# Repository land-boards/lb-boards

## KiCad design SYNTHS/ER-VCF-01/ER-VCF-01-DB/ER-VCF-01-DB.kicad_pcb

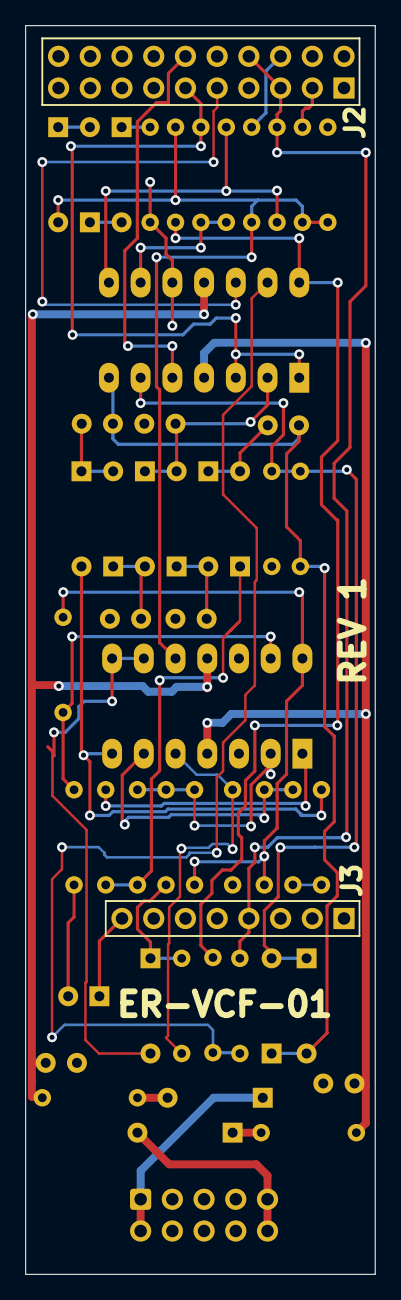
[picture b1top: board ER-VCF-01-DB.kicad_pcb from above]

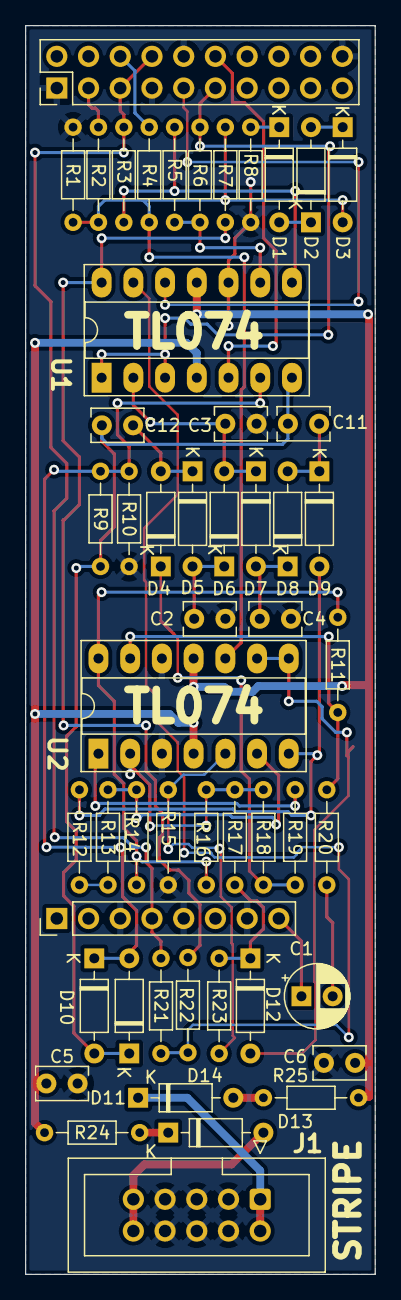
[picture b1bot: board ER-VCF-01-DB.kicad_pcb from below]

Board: 2 copper layers, 28.0 x 100.0 mm, 52 parts (52 on the bottom side), 41 nets.

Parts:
C1: 1uF; CP_Radial_D5.0mm_P2.50mm
C2, C3, C4, C11, C12: 1nF; C_Rect_L4.0mm_W2.5mm_P2.50mm
C5, C6: 0.1uF; C_Rect_L4.0mm_W2.5mm_P2.50mm
D1, D2, D3, D4, D5, D6, D7, D8, D9, D10, D11, D12, D13, D14: 1N4148; D_DO-35_SOD27_P7.62mm_Horizontal
J1: HEADER, 2X5; IDC-Header_2x05_P2.54mm_Vertical
J2: HEADER, 2X10; PinHeader_2x10_P2.54mm_Vertical
J3: HEADER, 1x8; PinHeader_1x08_P2.54mm_Vertical
R1, R9: 10K; R_Axial_DIN0204_L3.6mm_D1.6mm_P7.62mm_Horizontal
R2, R4, R7, R20, R21, R22: 100K; R_Axial_DIN0204_L3.6mm_D1.6mm_P7.62mm_Horizontal
R3, R6, R8, R11: 1K; R_Axial_DIN0204_L3.6mm_D1.6mm_P7.62mm_Horizontal
R5: 47K; R_Axial_DIN0204_L3.6mm_D1.6mm_P7.62mm_Horizontal
R10, R12, R19: 2.2K; R_Axial_DIN0204_L3.6mm_D1.6mm_P7.62mm_Horizontal
R13, R14, R15, R16, R17, R18, R23: 33K; R_Axial_DIN0204_L3.6mm_D1.6mm_P7.62mm_Horizontal
R24, R25: 10; R_Axial_DIN0204_L3.6mm_D1.6mm_P7.62mm_Horizontal
U1, U2: TL074; DIP-14_W7.62mm_Socket_LongPads

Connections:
+12V: C5.1, R24.2, U1.4 (V+), U2.4 (V+)
-12V: C6.2, R25.2, U1.11 (V-), U2.11 (V-)
/AUDIO: R11.2, R14.1, R16.1, U2.14
/CV: D12.1 (K), R17.1, R23.1
/J1-T: C1.1, J3.8
/J2-T: J2.5, J2.8, J3.4, R3.1, R21.1
/POT2-2: J2.9, U1.12 (+)
/POT4-2: J2.6, R4.1
/POT5-1: J2.11, R6.2, U1.1, U1.3 (+)
/POT5-2: J2.12, U1.5 (+)
/POT6-2: J2.3, R2.1
GND: C2.2, C3.2, C4.2, C5.2, C6.1, J1.3, J1.4, J1.5, J1.6, J1.7, J1.8, J2.1, J2.7, J2.10, J2.20, J3.3, J3.5, J3.7, R1.1, R8.1, R10.1, R15.1, U1.10 (+), U2.3 (+), U2.12 (+)
unnamed: C1.2, R20.1
unnamed: C2.1, D7.2 (A), D8.1 (K)
unnamed: C3.1, D6.2 (A), D7.1 (K), U1.2 (-)
unnamed: C4.1, D5.2 (A), D6.1 (K)
unnamed: C11.1, C12.1, D10.2 (A), D11.1 (K), R9.1, U1.7
unnamed: C11.2, D8.2 (A), D9.1 (K)
unnamed: C12.2, D4.2 (A), D5.1 (K)
unnamed: D1.1 (K), R8.2
unnamed: D1.2 (A), D2.1 (K)
unnamed: D2.2 (A), D3.1 (K)
unnamed: D3.2 (A), R1.2, R2.2, R4.2, R7.2, U2.10 (+)
unnamed: D4.1 (K), R18.2, R19.2
unnamed: D9.2 (A), R12.1, U2.7
unnamed: D10.1 (K), D11.2 (A), R9.2, R10.2, U1.6 (-)
unnamed: D12.2 (A), U2.8, U2.9 (-)
unnamed: D13.1 (K), R24.1
unnamed: D13.2 (A), J1.9, J1.10
unnamed: D14.1 (K), J1.1, J1.2
unnamed: D14.2 (A), R25.1
unnamed: R3.2, R5.2, U1.8
unnamed: R5.1, R6.1, U1.9 (-)
unnamed: R11.1, R20.2, U2.13 (-)
unnamed: R12.2, R13.2
unnamed: R13.1, R14.2, U2.6 (-)
unnamed: R15.2, R23.2, U2.5 (+)
unnamed: R16.2, R17.2, R18.1, U2.2 (-)
unnamed: R19.1, U2.1
unnamed: R21.2, R22.1, U1.13 (-)
unnamed: R7.1, R22.2, U1.14

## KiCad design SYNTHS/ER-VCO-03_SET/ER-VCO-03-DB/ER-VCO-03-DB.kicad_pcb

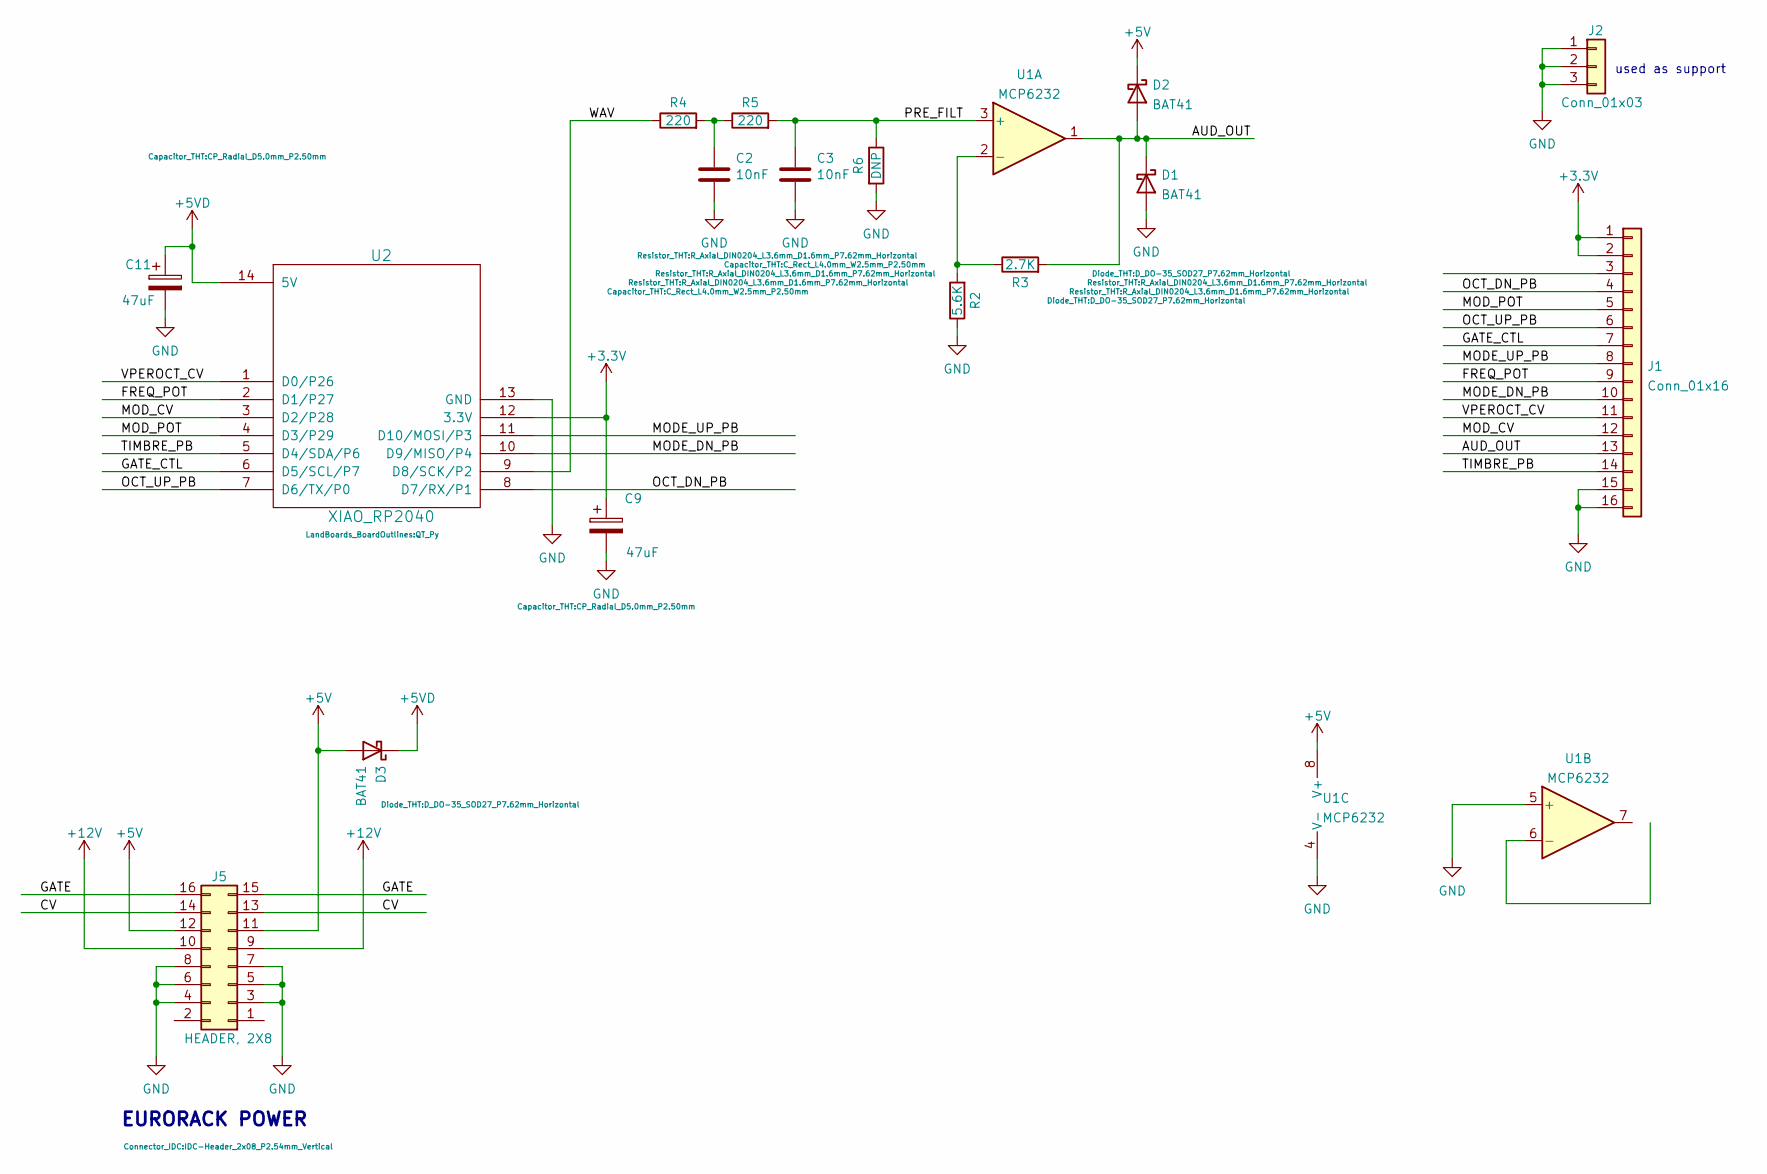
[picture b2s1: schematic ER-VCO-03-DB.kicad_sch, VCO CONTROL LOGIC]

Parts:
C2, C3: 10nF; C_Rect_L4.0mm_W2.5mm_P2.50mm
C9, C11: 47uF; CP_Radial_D5.0mm_P2.50mm
D1, D2, D3: BAT41; D_DO-35_SOD27_P7.62mm_Horizontal
J1: Conn_01x16; PinHeader_2x08_P2.54mm_Vertical
J2: Conn_01x03; PinHeader_1x03_P2.54mm_Vertical
J5: HEADER, 2X8; IDC-Header_2x08_P2.54mm_Vertical
R2: 5.6K; R_Axial_DIN0204_L3.6mm_D1.6mm_P7.62mm_Horizontal
R3: 2.7K; R_Axial_DIN0204_L3.6mm_D1.6mm_P7.62mm_Horizontal
R4, R5: 220; R_Axial_DIN0204_L3.6mm_D1.6mm_P7.62mm_Horizontal
R6: DNP; R_Axial_DIN0204_L3.6mm_D1.6mm_P7.62mm_Horizontal
U1: MCP6232; DIP-8_W7.62mm
U2: XIAO_RP2040; QT_Py

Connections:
+3V3: C9.1, J1.1, J1.2, U2.12 (3.3V)
+5V: D2.1 (K), D3.2 (A), J5.11, J5.12, U1.8 (V+)
+5VD: C11.1, D3.1 (K), U2.14 (5V)
+12V: J5.9, J5.10
/AUD_OUT: D1.1 (K), D2.2 (A), J1.13, R3.2, U1.1
/CV: J5.13, J5.14
/FREQ_POT: J1.9, U2.2 (D1/P27)
/GATE: J5.15, J5.16
/GATE_CTL: J1.7, U2.6 (D5/SCL/P7)
/MODE_DN_PB: J1.10, U2.10 (D9/MISO/P4)
/MODE_UP_PB: J1.8, U2.11 (D10/MOSI/P3)
/MOD_CV: J1.12, U2.3 (D2/P28)
/MOD_POT: J1.5, U2.4 (D3/P29)
/OCT_DN_PB: J1.4, U2.8 (D7/RX/P1)
/OCT_UP_PB: J1.6, U2.7 (D6/TX/P0)
/PRE_FILT: C3.1, R5.2, R6.1, U1.3 (+)
/TIMBRE_PB: J1.14, U2.5 (D4/SDA/P6)
/VPEROCT_CV: J1.11, U2.1 (D0/P26)
/WAV: R4.1, U2.9 (D8/SCK/P2)
GND: C2.2, C3.2, C9.2, C11.2, D1.2 (A), J1.15, J1.16, J2.1, J2.2, J2.3, J5.3, J5.4, J5.5, J5.6, J5.7, J5.8, R2.1, R6.2, U1.4 (V-), U1.5 (+), U2.13 (GND)
unnamed: C2.1, R4.2, R5.1
unnamed: R2.2, R3.1, U1.2 (-)

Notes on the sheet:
used as support
EURORACK POWER

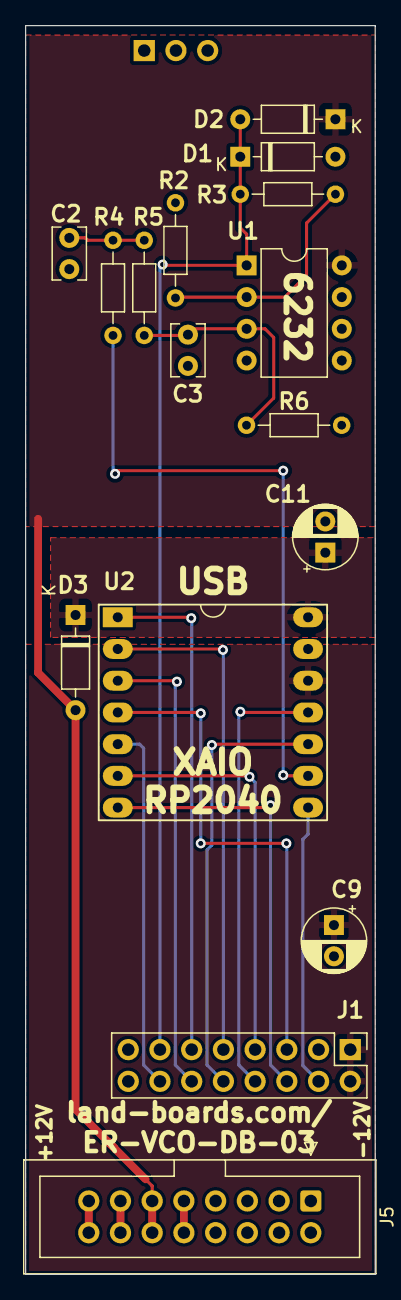
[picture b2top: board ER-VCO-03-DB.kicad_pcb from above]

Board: 2 copper layers, 28.0 x 100.0 mm, 17 parts (1 on the bottom side), 22 nets.

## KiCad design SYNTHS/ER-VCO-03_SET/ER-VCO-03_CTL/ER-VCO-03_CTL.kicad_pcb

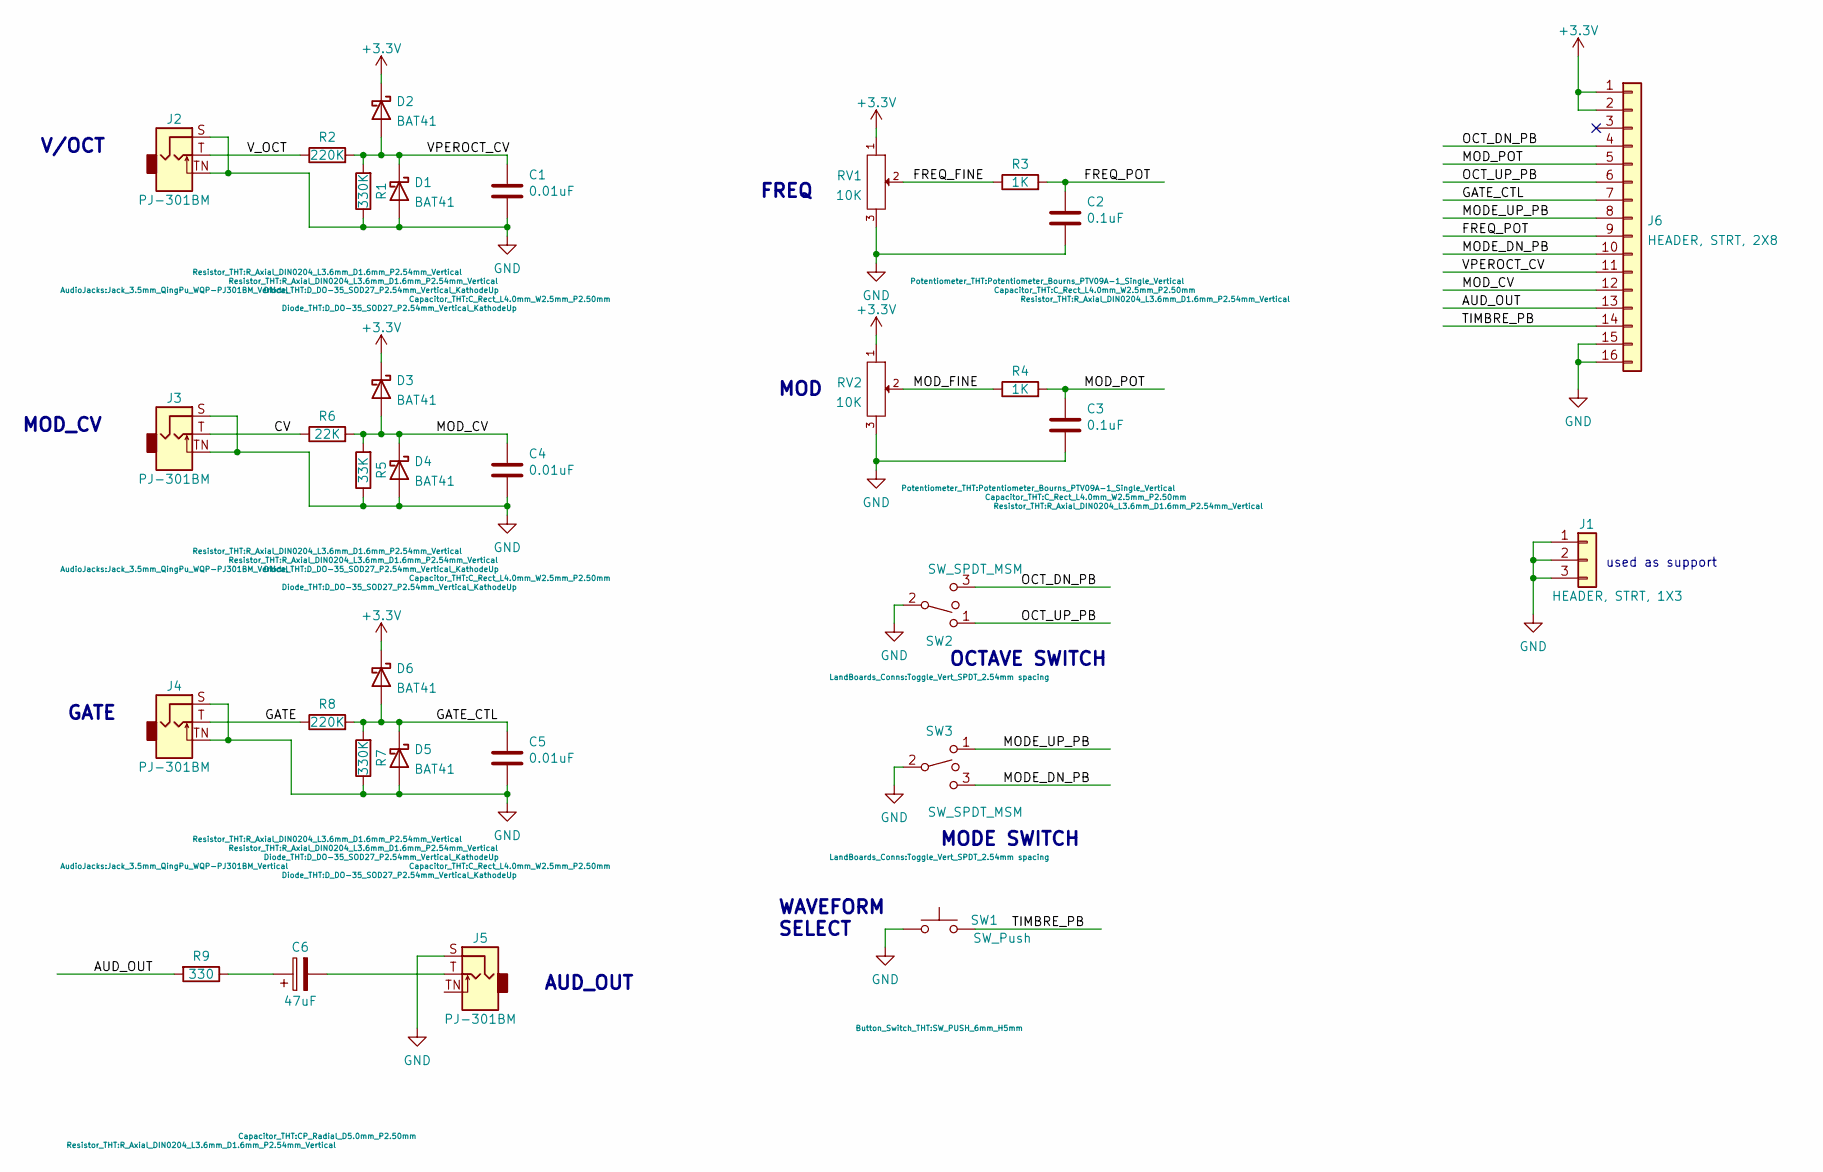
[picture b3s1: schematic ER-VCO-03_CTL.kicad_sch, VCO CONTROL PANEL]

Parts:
C1, C4, C5: 0.01uF; C_Rect_L4.0mm_W2.5mm_P2.50mm
C2, C3: 0.1uF; C_Rect_L4.0mm_W2.5mm_P2.50mm
C6: 47uF; CP_Radial_D5.0mm_P2.50mm
D1, D2, D3, D4, D5, D6: BAT41; D_DO-35_SOD27_P2.54mm_Vertical_KathodeUp
J1: HEADER, STRT, 1X3; PinHeader_1x03_P2.54mm_Vertical
J2, J3, J4, J5: PJ-301BM; Jack_3.5mm_QingPu_WQP-PJ301BM_Vertical
J6: HEADER, STRT, 2X8; PinHeader_2x08_P2.54mm_Vertical
R1, R7: 330K; R_Axial_DIN0204_L3.6mm_D1.6mm_P2.54mm_Vertical
R2, R8: 220K; R_Axial_DIN0204_L3.6mm_D1.6mm_P2.54mm_Vertical
R3, R4: 1K; R_Axial_DIN0204_L3.6mm_D1.6mm_P2.54mm_Vertical
R5: 33K; R_Axial_DIN0204_L3.6mm_D1.6mm_P2.54mm_Vertical
R6: 22K; R_Axial_DIN0204_L3.6mm_D1.6mm_P2.54mm_Vertical
R9: 330; R_Axial_DIN0204_L3.6mm_D1.6mm_P2.54mm_Vertical
RV1, RV2: 10K; Potentiometer_Bourns_PTV09A-1_Single_Vertical
SW1: SW_Push; SW_PUSH_6mm_H5mm
SW2, SW3: SW_SPDT_MSM; Toggle_Vert_SPDT_2.54mm spacing

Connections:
+3V3: D2.1 (K), D3.1 (K), D6.1 (K), J6.1, J6.2, RV1.1, RV2.1
/AUD_OUT: J6.13, R9.2
/CV: J3.T, R6.1
/FREQ_FINE: R3.1, RV1.2
/FREQ_POT: C2.1, J6.9, R3.2
/GATE: J4.T, R8.1
/GATE_CTL: C5.1, D5.1 (K), D6.2 (A), J6.7, R7.2, R8.2
/MODE_DN_PB: J6.10, SW3.3
/MODE_UP_PB: J6.8, SW3.1
/MOD_CV: C4.1, D3.2 (A), D4.1 (K), J6.12, R5.2, R6.2
/MOD_FINE: R4.1, RV2.2
/MOD_POT: C3.1, J6.5, R4.2
/OCT_DN_PB: J6.4, SW2.3
/OCT_UP_PB: J6.6, SW2.1
/TIMBRE_PB: J6.14, SW1.2
/VPEROCT_CV: C1.1, D1.1 (K), D2.2 (A), J6.11, R1.2, R2.2
/V_OCT: J2.T, R2.1
GND: C1.2, C2.2, C3.2, C4.2, C5.2, D1.2 (A), D4.2 (A), D5.2 (A), J1.1, J1.2, J1.3, J2.S, J2.TN, J3.S, J3.TN, J4.S, J4.TN, J5.S, J6.15, J6.16, R1.1, R5.1, R7.1, RV1.3, RV2.3, SW1.1, SW2.2, SW3.2
unnamed: C6.1, R9.1
unnamed: C6.2, J5.T

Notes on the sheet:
OCTAVE SWITCH
GATE
used as support
V/OCT
MOD_CV
FREQ
MODE SWITCH
WAVEFORM SELECT
MOD
AUD_OUT

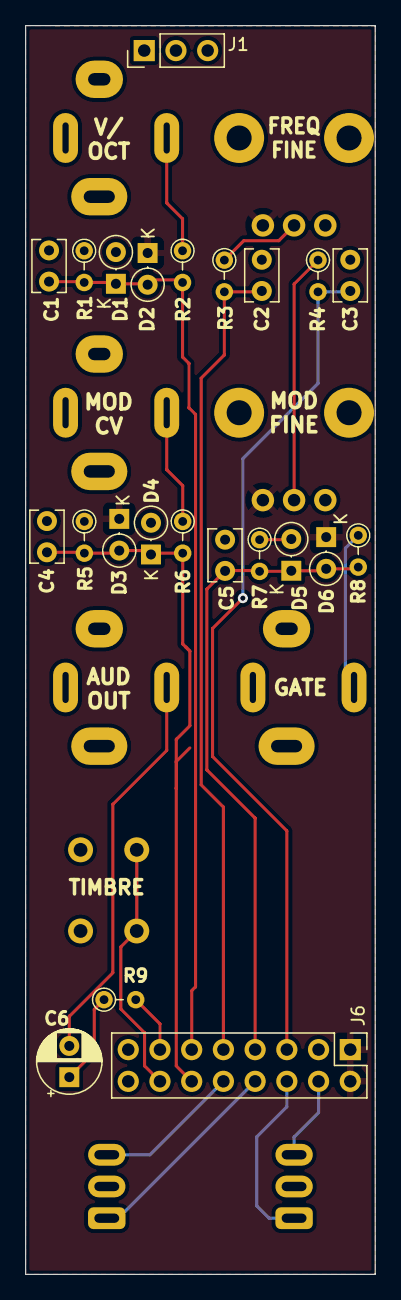
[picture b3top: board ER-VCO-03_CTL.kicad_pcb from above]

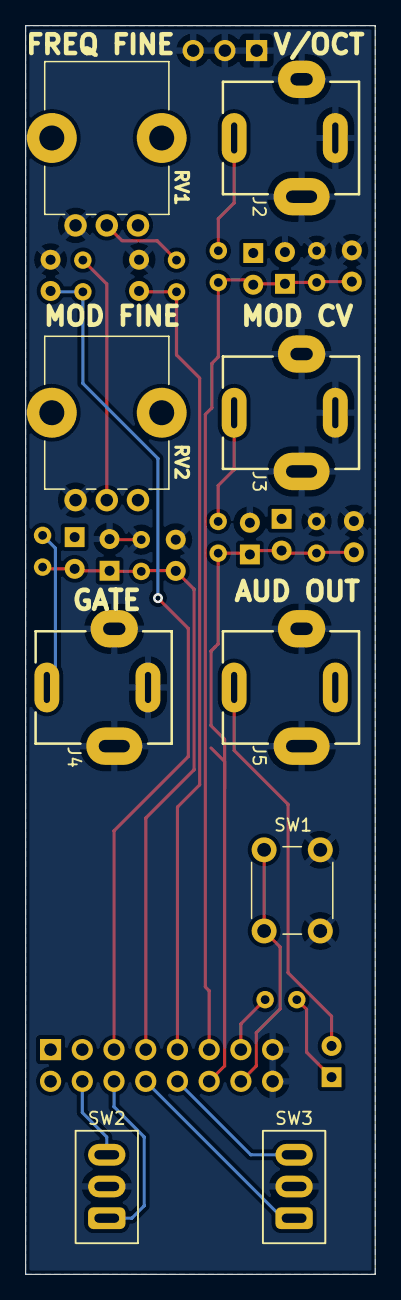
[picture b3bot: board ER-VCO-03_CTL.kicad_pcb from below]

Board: 2 copper layers, 28.0 x 100.0 mm, 32 parts (9 on the bottom side), 20 nets.
